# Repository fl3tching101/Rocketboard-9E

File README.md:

# Rocketboard-9E
Very basic 3x3 macropad that uses the Rocketboard Engine as its controller.

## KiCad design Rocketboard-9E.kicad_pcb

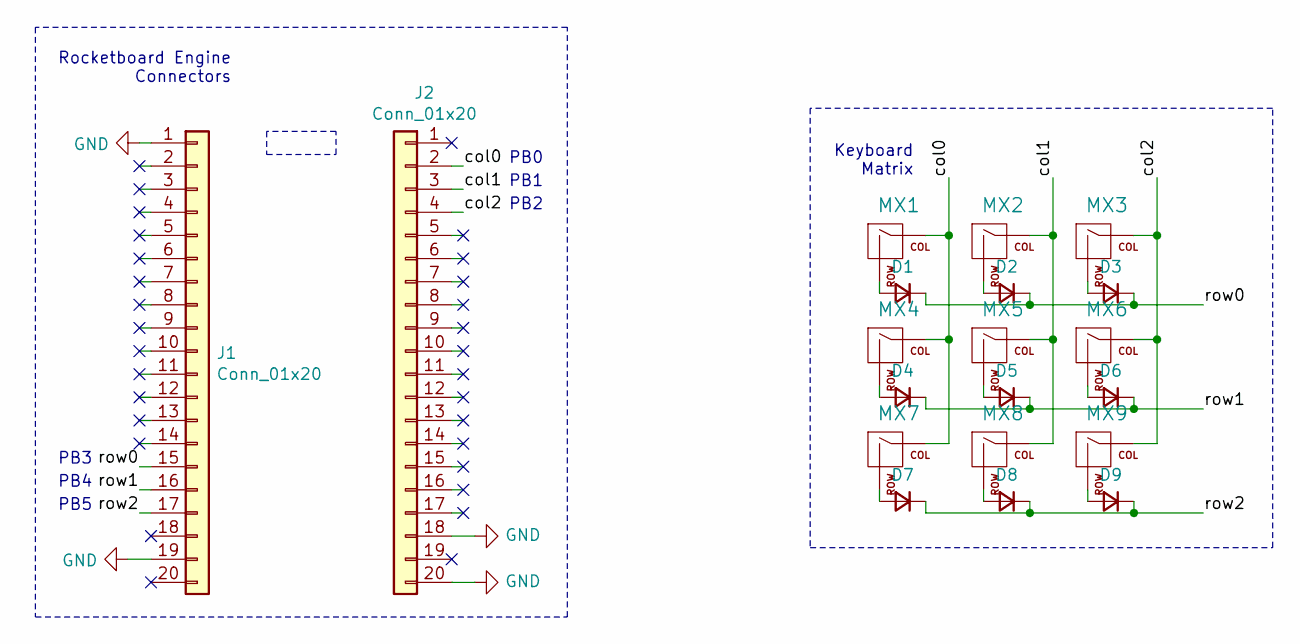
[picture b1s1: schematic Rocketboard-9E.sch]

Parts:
D1, D2, D3, D4, D5, D6, D7, D8, D9: D_Small; D_SOD-123
J1, J2: Conn_01x20; PinHeader_1x20_P2.54mm_Vertical
MX1, MX2, MX3, MX4, MX5, MX6, MX7, MX8, MX9: MX-NoLED; MXOnly-1U-NoLED

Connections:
/col0: J2.2, MX1.1 (COL), MX4.1 (COL), MX7.1 (COL)
/col1: J2.3, MX2.1 (COL), MX5.1 (COL), MX8.1 (COL)
/col2: J2.4, MX3.1 (COL), MX6.1 (COL), MX9.1 (COL)
/row0: D1.1 (K), D2.1 (K), D3.1 (K), J1.15
/row1: D4.1 (K), D5.1 (K), D6.1 (K), J1.16
/row2: D7.1 (K), D8.1 (K), D9.1 (K), J1.17
GND: J1.1, J1.19, J2.18, J2.20
unnamed: D1.2 (A), MX1.2 (ROW)
unnamed: D2.2 (A), MX2.2 (ROW)
unnamed: D3.2 (A), MX3.2 (ROW)
unnamed: D4.2 (A), MX4.2 (ROW)
unnamed: D5.2 (A), MX5.2 (ROW)
unnamed: D6.2 (A), MX6.2 (ROW)
unnamed: D7.2 (A), MX7.2 (ROW)
unnamed: D8.2 (A), MX8.2 (ROW)
unnamed: D9.2 (A), MX9.2 (ROW)

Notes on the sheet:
PB0
PB1
PB2
PB3
PB4
PB5
Rocketboard Engine Connectors
Keyboard Matrix

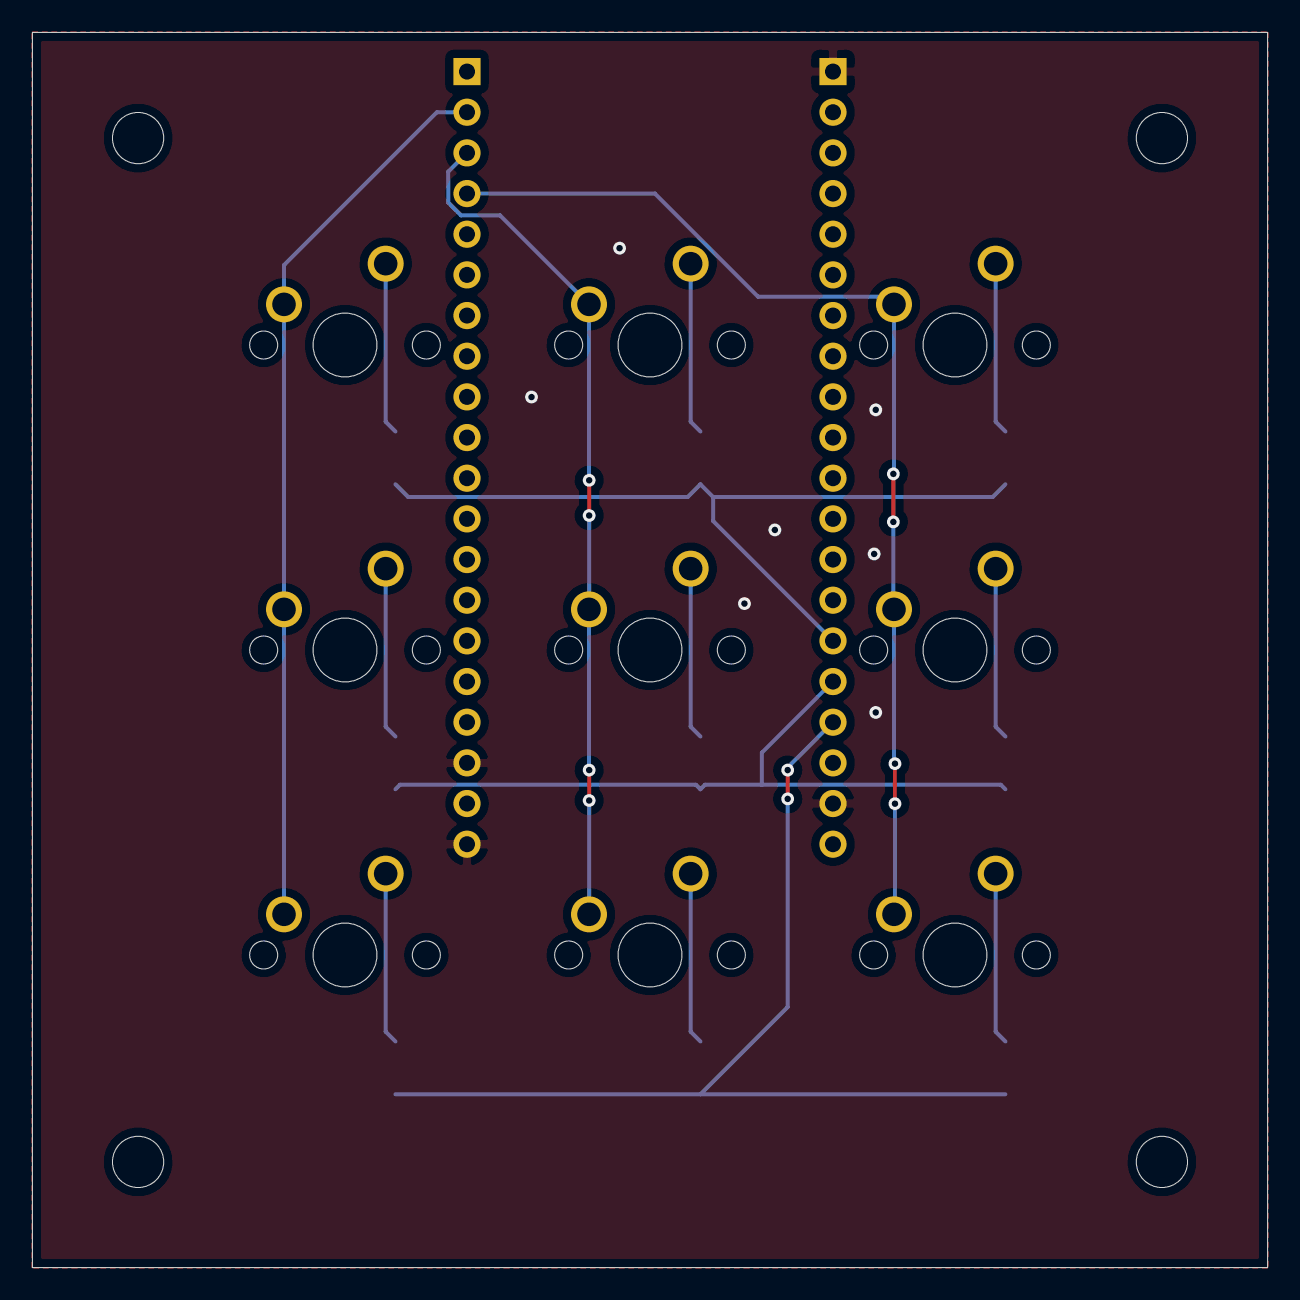
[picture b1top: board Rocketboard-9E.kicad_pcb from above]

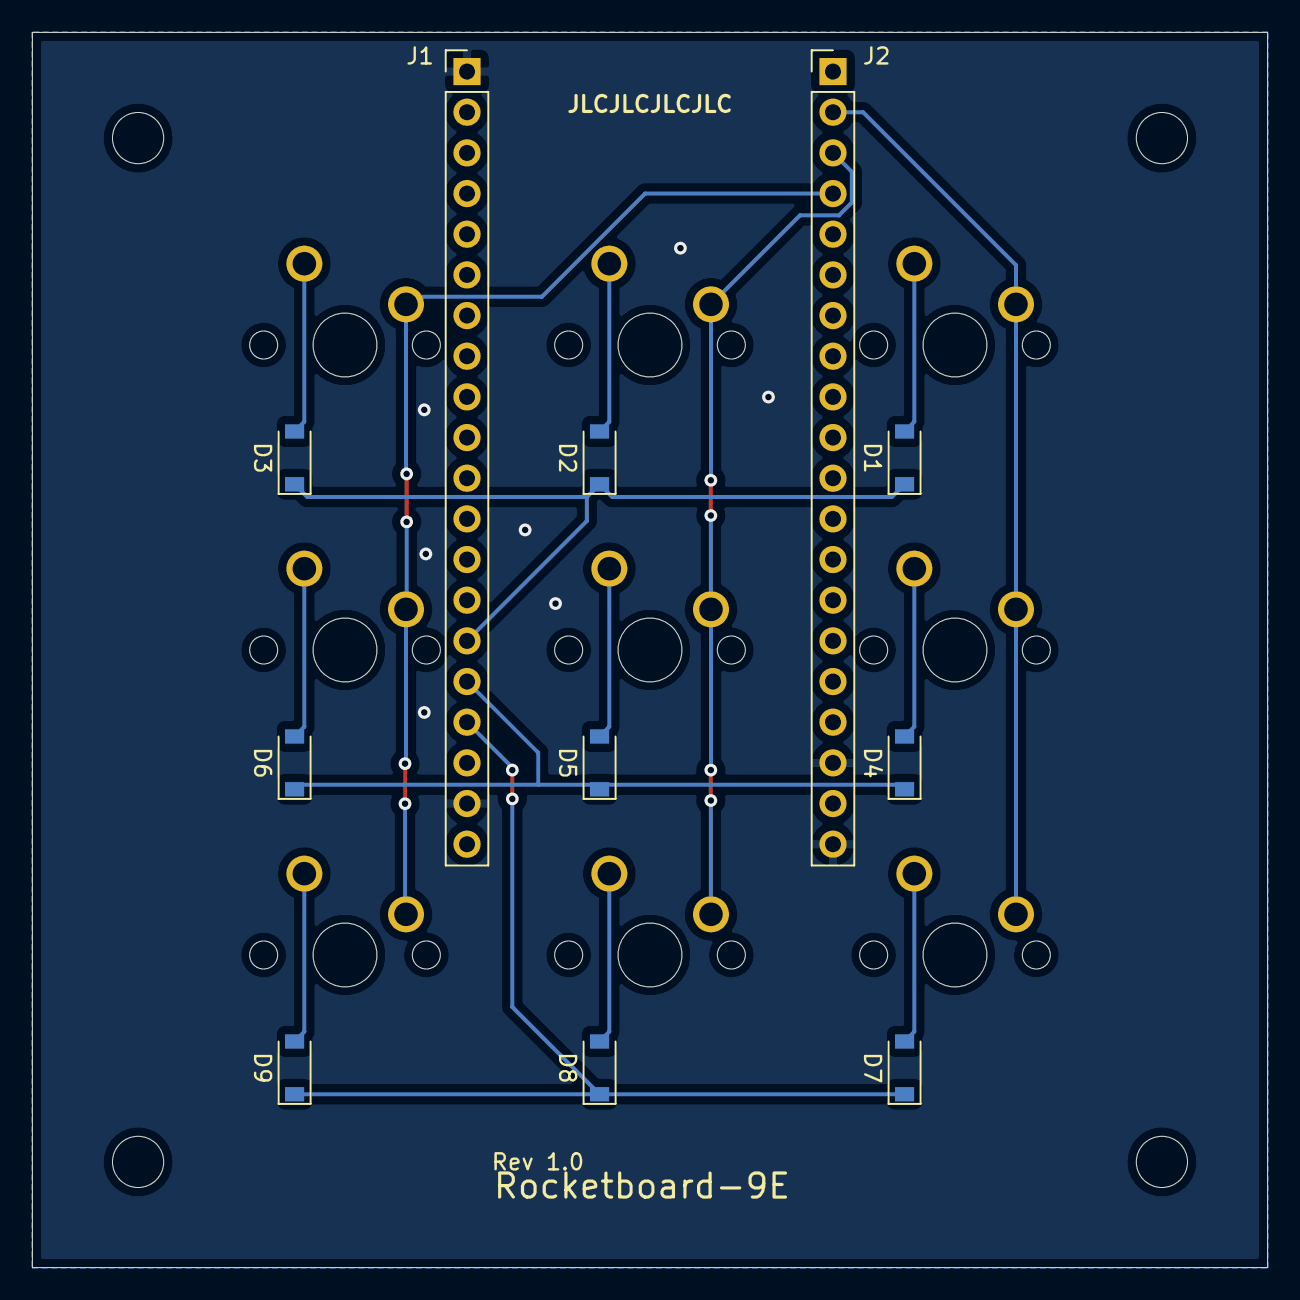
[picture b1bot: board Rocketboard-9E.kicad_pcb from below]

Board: 2 copper layers, 77.1 x 77.2 mm, 20 parts (11 on the bottom side), 16 nets.

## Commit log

2021-09-03 Rev 1.0 as ordered from JLCPCB
2021-09-03 Exported schematic and layout PDFs for easier veiwing
2021-12-11 Added image
2021-12-11 Added README with image
